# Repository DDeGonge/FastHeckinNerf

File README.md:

# FastHeckinNerf
Nerf gun go brapp but like way more than you'd think

# cad is on Onshape
[click here](https://cad.onshape.com/documents/74a6ce56696b18f03596ff0c/w/5040f2fdc5ac761a49e53a9d/e/2b4bafe3441c51fd1e40706f?renderMode=0&uiState=649b69e7189e940572b81350)

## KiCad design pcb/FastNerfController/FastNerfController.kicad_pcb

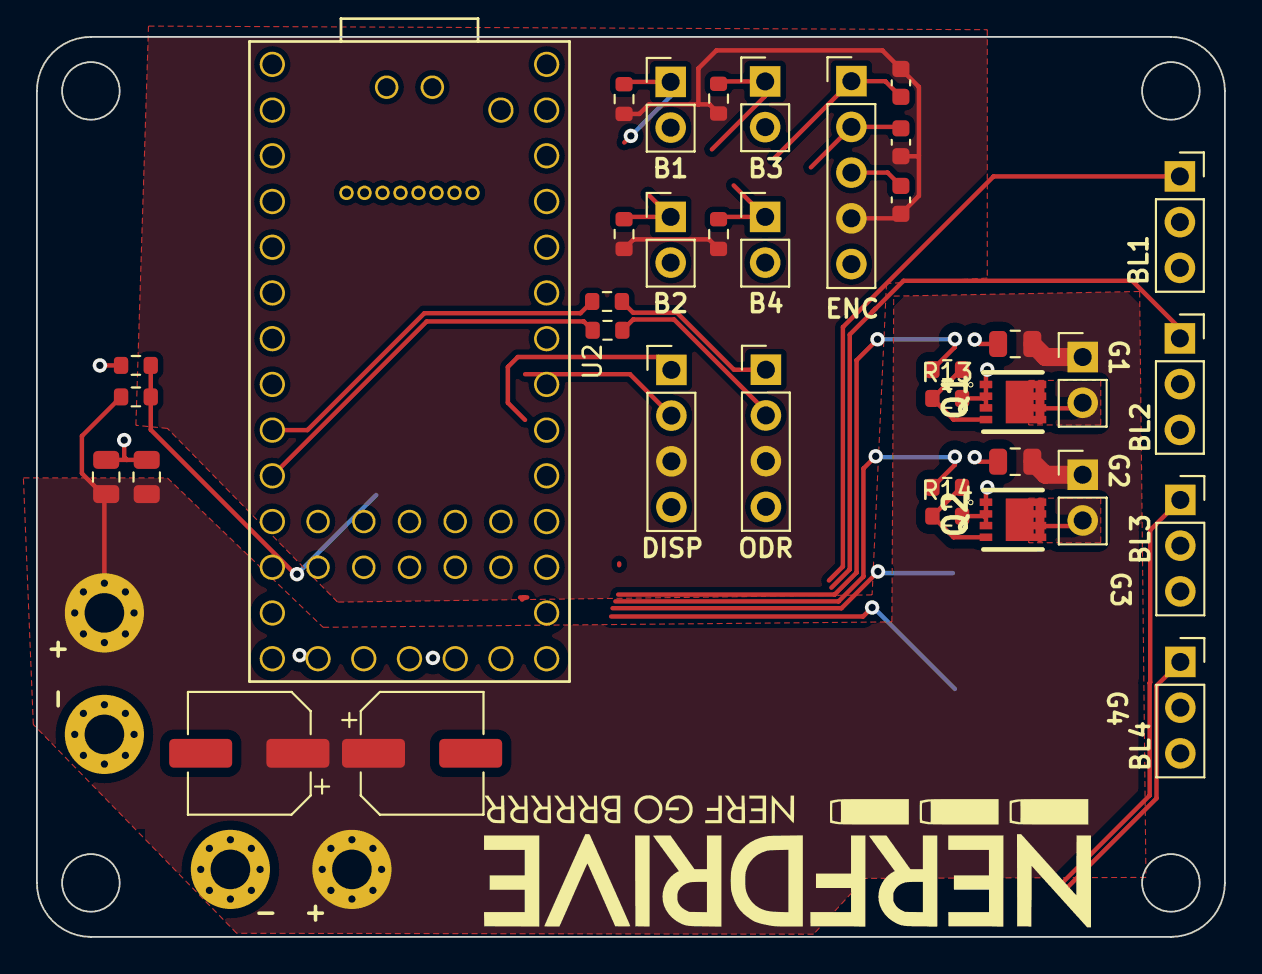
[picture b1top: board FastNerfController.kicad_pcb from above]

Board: 2 copper layers, 66.0 x 50.0 mm, 41 parts (0 on the bottom side), 27 nets.

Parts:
C1, C2: 47uF; CP_Elec_6.3x5.8
C3, C4, C5, C6: 10uF; C_0805_2012Metric
C9, C10, C11: 0.1uF; C_0603_1608Metric
J1, J2, J3, J4: Conn_01x03; PinSocket_1x03_P2.54mm_Vertical
J5, J6, J11, J12: Conn_01x01; MountingHole_2.2mm_M2_Pad_Via
J7, J8, J16, J17, J18, J19: Conn_01x02; PinHeader_1x02_P2.54mm_Vertical
J13, J14: Conn_01x04; PinHeader_1x04_P2.54mm_Vertical
J15: Conn_01x05; PinHeader_1x05_P2.54mm_Vertical
Q1, Q2: DMG7430LFG-7; POWERDI-3333-8
R1, R2, R11, R12: 100; R_0603_1608Metric
R5: 90k; R_0603_1608Metric
R6, R7, R8, R9, R10: 10k; R_0603_1608Metric
R13, R14: 2.2k; R_0603_1608Metric
U2: Teensy4.0; Teensy40_SMT

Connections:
+3.3V: C9.1, C10.1, C11.1, J13.3, J14.3, J15.4, R7.1, R8.1, R9.1, R10.1
/BLDC 1: J1.1, U2.4 (2_OUT2)
/BLDC 2: J2.1, U2.5 (3_LRCLK2)
/BLDC 3: J3.1, U2.6 (4_BCLK2)
/BLDC 4: J4.1, U2.7 (5_IN2)
/BTN: C11.2, J15.3, U2.22 (15_A1_RX3_SPDIF_IN)
/Battery_V: R5.2, R6.1, U2.21 (14_A0_TX3_SPDIF_OUT)
/Button1: J16.1, R7.2, U2.2 (0_RX1_CRX2_CS1)
/Button2: J17.1, R8.2, U2.3 (1_TX1_CTX2_MISO1)
/Button3: J18.1, R9.2, U2.13 (11_MOSI_CTX1)
/Button4: J19.1, R10.2, U2.14 (12_MISO_MQSL)
/DIR: C10.2, J15.2, U2.23 (16_A2_RX4_SCL1)
/Gate1: R1.2, U2.11 (9_OUT1C)
/Gate2: R2.2, U2.12 (10_CS_MQSR)
/PULSE: C9.2, J15.1, U2.24 (17_A3_TX4_SDA1)
/RX: J13.1, R11.1
/SCL: J14.2, U2.26 (19_A5_SCL0)
/SDA: J14.1, U2.25 (18_A4_SDA0)
/TX: J13.2, R12.1
GND: C1.2, C2.2, C3.2, C4.2, C5.2, C6.2, J1.3, J2.3, J3.3, J4.3, J6.1, J12.1, J13.4, J14.4, J15.5, J16.2, J17.2, J18.2, J19.2, Q1.1 (S_1), Q1.2 (S_2), Q1.3 (S_3), Q2.1 (S_1), Q2.2 (S_2), Q2.3 (S_3), R6.2, R13.2, R14.2, U2.1 (GND), U2.32 (GND)
unnamed: Q1.5 (D_1), Q1.6 (D_2), Q1.7 (D_3), Q1.8 (D_4)
unnamed: Q2.5 (D_1), Q2.6 (D_2), Q2.7 (D_3), Q2.8 (D_4)
unnamed: R1.1, R13.1
unnamed: R2.1, R14.1
unnamed: R11.2, U2.9 (7_RX2_OUT1A)
unnamed: R12.2, U2.10 (8_TX2_IN1)
VCC: C1.1, C2.1, C3.1, C4.1, C5.1, C6.1, J5.1, J7.1, J8.1, J11.1, R5.1

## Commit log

2023-06-27 push it all
2023-06-27 remove deprecated cad, its on Onshape now!
2023-06-27 add onshape link to readme
2023-09-04 fix pcb and other stuff
2024-04-15 push
2024-07-02 big push
